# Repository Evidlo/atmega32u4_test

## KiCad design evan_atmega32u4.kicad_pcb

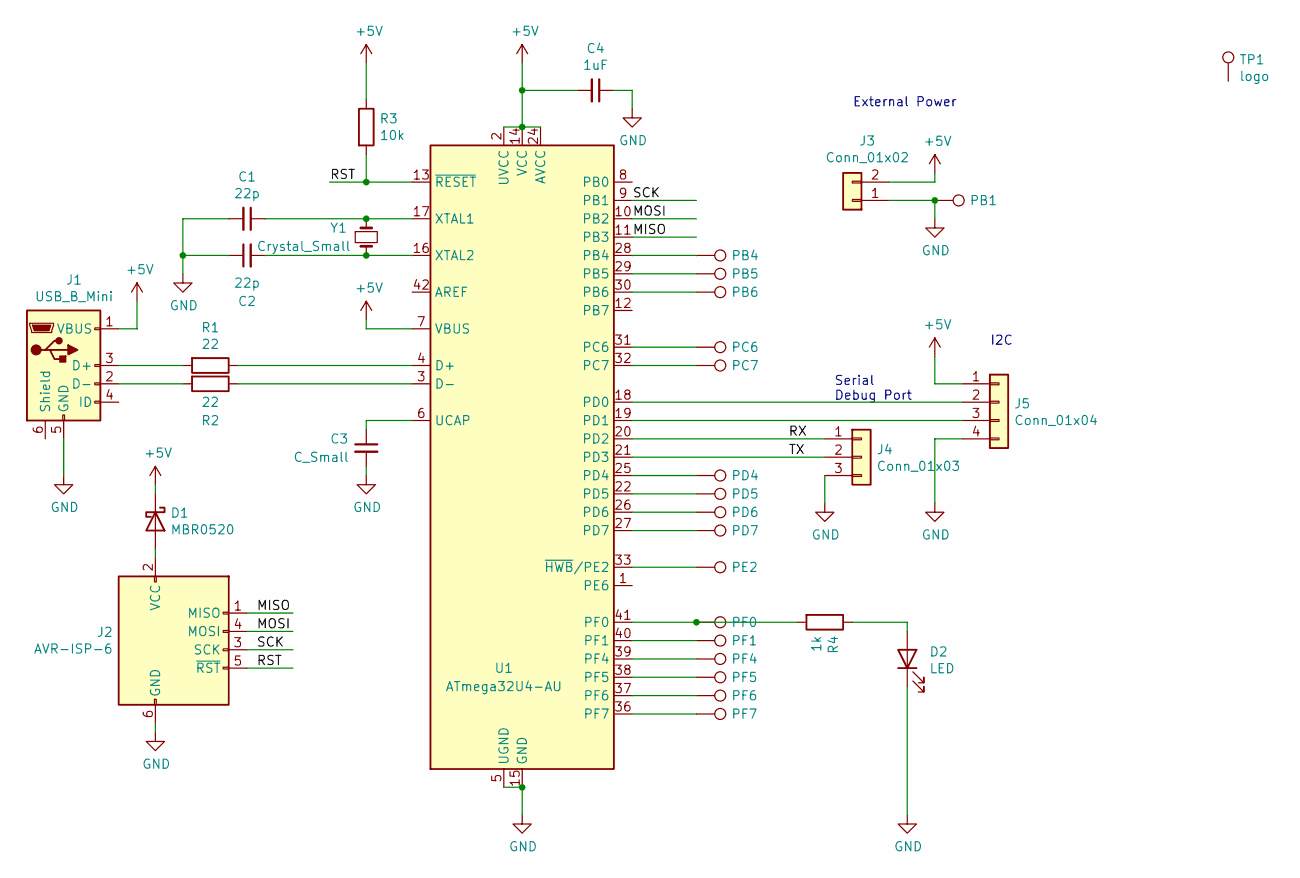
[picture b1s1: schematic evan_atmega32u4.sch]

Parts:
C1, C2: 22p; C_0805_2012Metric_Pad1.18x1.45mm_HandSolder
C3: C_Small; C_0805_2012Metric_Pad1.18x1.45mm_HandSolder
C4: 1uF; C_0805_2012Metric_Pad1.18x1.45mm_HandSolder
D1: MBR0520; D_SOD-123
D2: LED; LED_D3.0mm
J1: USB_B_Mini; USB_Mini-B_Wuerth_65100516121_Horizontal
J2: AVR-ISP-6; IDC-Header_2x03_P2.54mm_Vertical
J3: Conn_01x02; Molex_KK-254_AE-6410-02A_1x02_P2.54mm_Vertical
J4: Conn_01x03; Molex_KK-254_AE-6410-03A_1x03_P2.54mm_Vertical
J5: Conn_01x04; Molex_KK-254_AE-6410-04A_1x04_P2.54mm_Vertical
PB1, PB4, PB5, PB6: TestPoint; TestPoint_THTPad_D2.0mm_Drill1.0mm
PC6, PC7: TestPoint; TestPoint_THTPad_D2.0mm_Drill1.0mm
PD4, PD5, PD6, PD7: TestPoint; TestPoint_THTPad_D2.0mm_Drill1.0mm
PE2: TestPoint; TestPoint_THTPad_D2.0mm_Drill1.0mm
PF0, PF1, PF4, PF5, PF6, PF7: TestPoint; TestPoint_THTPad_D2.0mm_Drill1.0mm
R1, R2: 22; R_0805_2012Metric_Pad1.20x1.40mm_HandSolder
R3: 10k; R_0805_2012Metric_Pad1.20x1.40mm_HandSolder
R4: 1k; R_0805_2012Metric_Pad1.20x1.40mm_HandSolder
TP1: logo; phil
U1: ATmega32U4-AU; TQFP-44_10x10mm_P0.8mm
Y1: Crystal_Small; Crystal_HC49-U_Vertical

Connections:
+5V: C4.2, D1.1 (K), J1.1 (VBUS), J3.2, J5.1, R3.1, U1.2 (UVCC), U1.7 (VBUS), U1.14 (VCC), U1.24 (AVCC), U1.34 (VCC), U1.44 (AVCC)
/MISO: J2.1 (MISO), U1.11 (PB3)
/MOSI: J2.4 (MOSI), U1.10 (PB2)
/RST: J2.5 (~RST), R3.2, U1.13 (~RESET)
/RX: J4.1, U1.20 (PD2)
/SCK: J2.3 (SCK), U1.9 (PB1)
/TX: J4.2, U1.21 (PD3)
GND: C1.2, C2.1, C3.2, C4.1, D2.1 (K), J1.5 (GND), J2.6 (GND), J3.1, J4.3, J5.4, PB1.1, U1.5 (UGND), U1.15 (GND), U1.23 (GND), U1.35 (GND), U1.43 (GND)
unnamed: C1.1, U1.17 (XTAL1), Y1.1
unnamed: C2.2, U1.16 (XTAL2), Y1.2
unnamed: C3.1, U1.6 (UCAP)
unnamed: D1.2 (A), J2.2 (VCC)
unnamed: D2.2 (A), R4.1
unnamed: J1.2 (D-), R2.2
unnamed: J1.3 (D+), R1.2
unnamed: J5.2, U1.18 (PD0)
unnamed: J5.3, U1.19 (PD1)
unnamed: PB4.1, U1.28 (PB4)
unnamed: PB5.1, U1.29 (PB5)
unnamed: PB6.1, U1.30 (PB6)
unnamed: PC6.1, U1.31 (PC6)
unnamed: PC7.1, U1.32 (PC7)
unnamed: PD4.1, U1.25 (PD4)
unnamed: PD5.1, U1.22 (PD5)
unnamed: PD6.1, U1.26 (PD6)
unnamed: PD7.1, U1.27 (PD7)
unnamed: PE2.1, U1.33 (~HWB~/PE2)
unnamed: PF0.1, R4.2, U1.41 (PF0)
unnamed: PF1.1, U1.40 (PF1)
unnamed: PF4.1, U1.39 (PF4)
unnamed: PF5.1, U1.38 (PF5)
unnamed: PF6.1, U1.37 (PF6)
unnamed: PF7.1, U1.36 (PF7)
unnamed: R1.1, U1.4 (D+)
unnamed: R2.1, U1.3 (D-)

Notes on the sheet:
Serial Debug Port
External Power
I2C

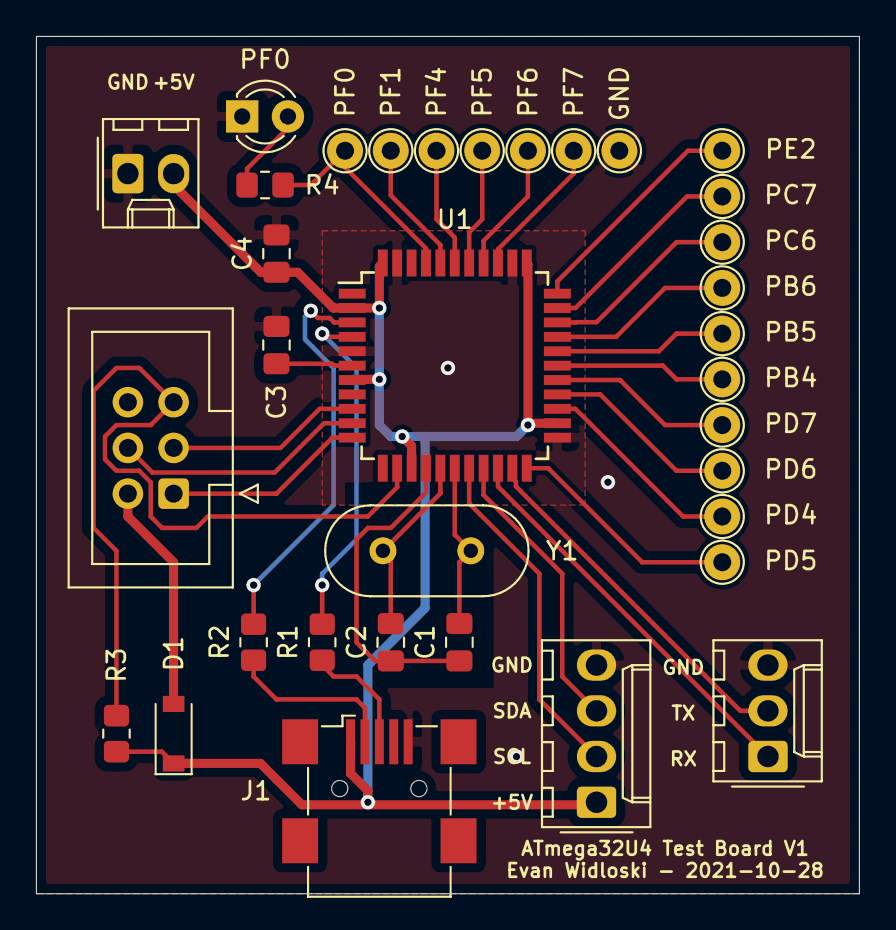
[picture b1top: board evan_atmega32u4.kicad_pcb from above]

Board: 2 copper layers, 45.7 x 47.6 mm, 35 parts (1 on the bottom side), 35 nets.

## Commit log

2021-11-09 init commit
2021-11-09 update cap value
